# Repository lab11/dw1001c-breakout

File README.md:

DWM1001 Breakout
================

Hardware files can be found in `hardware`.

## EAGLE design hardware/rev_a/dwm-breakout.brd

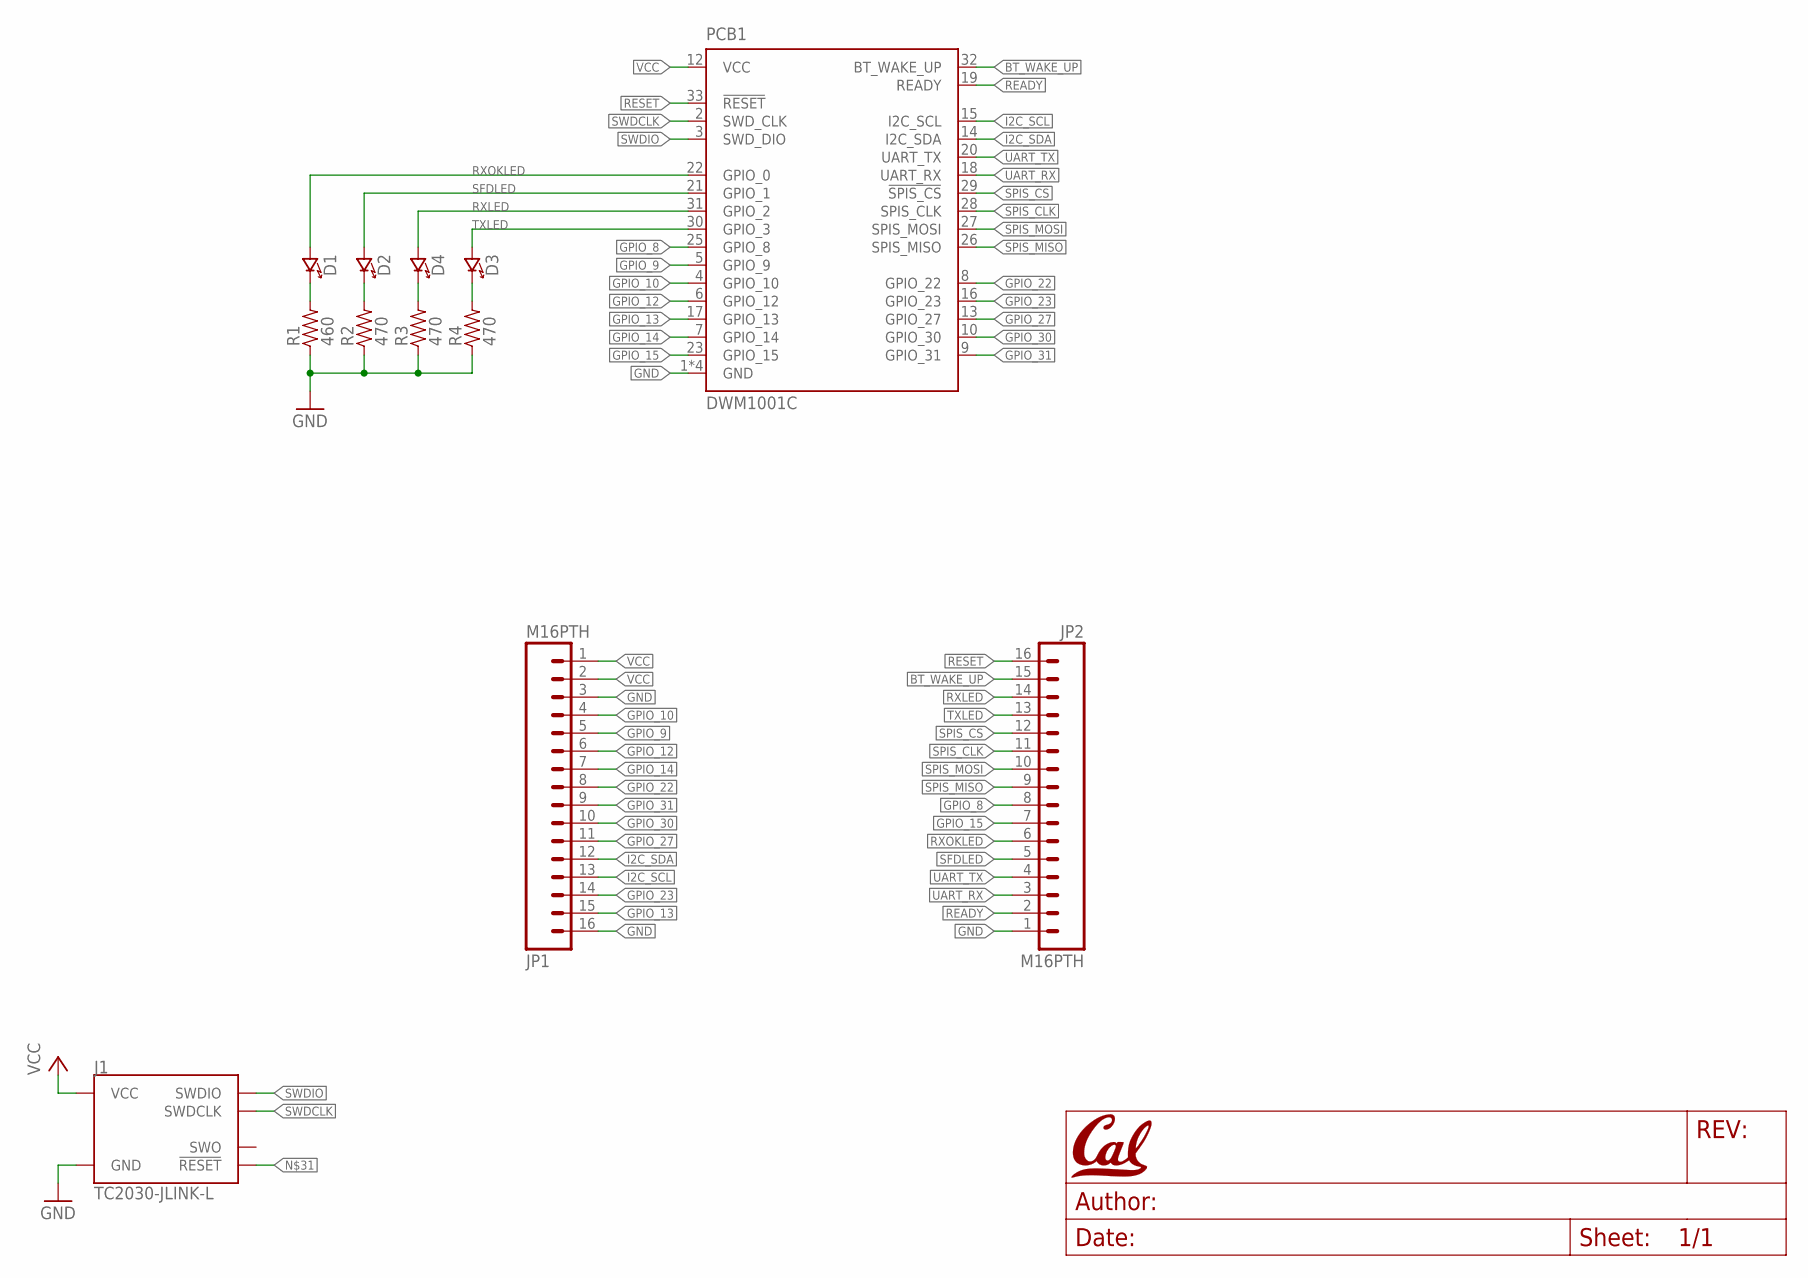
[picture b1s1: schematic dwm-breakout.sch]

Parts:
D1: LED0603; LED-0603; MPN LTST-C104KRKT; DIGIKEY 160-1835-6-ND
D2: LED0603; LED-0603; MPN LTST-C194TBKT; DIGIKEY 160-1837-6-ND
D3: LED0603; LED-0603; MPN LTST-C190YKT; DIGIKEY 160-1184-6-ND
D4: LED0603; LED-0603; MPN LTST-C194KGKT; DIGIKEY 160-1834-6-ND
J1: TC2030-JLINK-L; TC2030-IDC
JP1, JP2: M16PTH; 1X16
PCB1: DWM1001C
R1: 460; 0402_RES; MPN MCR01MZPJ471; DIGIKEY RHM470JCT-ND
R2, R3, R4: 470; 0402_RES; MPN MCR01MZPJ471; DIGIKEY RHM470JCT-ND

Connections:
!RESET: JP2.16, PCB1.33 (!RESET)
!SPIS_CS: JP2.12, PCB1.29 (!SPIS_CS)
BT_WAKE_UP: JP2.15, PCB1.32 (BT_WAKE_UP)
GND: J1.5 (GND), JP1.3, JP1.16, JP2.1, PCB1.1 (GND), PCB1.11 (GND), PCB1.24 (GND), PCB1.34 (GND), R1.1, R2.1, R3.1, R4.1
GPIO_8: JP2.8, PCB1.25 (GPIO_8)
GPIO_9: JP1.5, PCB1.5 (GPIO_9)
GPIO_10: JP1.4, PCB1.4 (GPIO_10)
GPIO_12: JP1.6, PCB1.6 (GPIO_12)
GPIO_13: JP1.15, PCB1.17 (GPIO_13)
GPIO_14: JP1.7, PCB1.7 (GPIO_14)
GPIO_15: JP2.7, PCB1.23 (GPIO_15)
GPIO_22: JP1.8, PCB1.8 (GPIO_22)
GPIO_23: JP1.14, PCB1.16 (GPIO_23)
GPIO_27: JP1.11, PCB1.13 (GPIO_27)
GPIO_30: JP1.10, PCB1.10 (GPIO_30)
GPIO_31: JP1.9, PCB1.9 (GPIO_31)
I2C_SCL: JP1.13, PCB1.15 (I2C_SCL)
I2C_SDA: JP1.12, PCB1.14 (I2C_SDA)
unnamed: D1.C (CATHODE), R1.2
unnamed: D2.C (CATHODE), R2.2
unnamed: D4.C (CATHODE), R3.2
unnamed: D3.C (CATHODE), R4.2
READY: JP2.2, PCB1.19 (READY)
RXLED: D4.A (ANODE), JP2.14, PCB1.31 (GPIO_2)
RXOKLED: D1.A (ANODE), JP2.6, PCB1.22 (GPIO_0)
SFDLED: D2.A (ANODE), JP2.5, PCB1.21 (GPIO_1)
SPIS_CLK: JP2.11, PCB1.28 (SPIS_CLK)
SPIS_MISO: JP2.9, PCB1.26 (SPIS_MISO)
SPIS_MOSI: JP2.10, PCB1.27 (SPIS_MOSI)
SWDCLK: J1.4 (SWDCLK), PCB1.2 (SWD_CLK)
SWDIO: J1.2 (SWDIO), PCB1.3 (SWD_DIO)
TXLED: D3.A (ANODE), JP2.13, PCB1.30 (GPIO_3)
UART_RX: JP2.3, PCB1.18 (UART_RX)
UART_TX: JP2.4, PCB1.20 (UART_TX)
VCC: J1.1 (VCC), JP1.1, JP1.2, PCB1.12 (VCC)

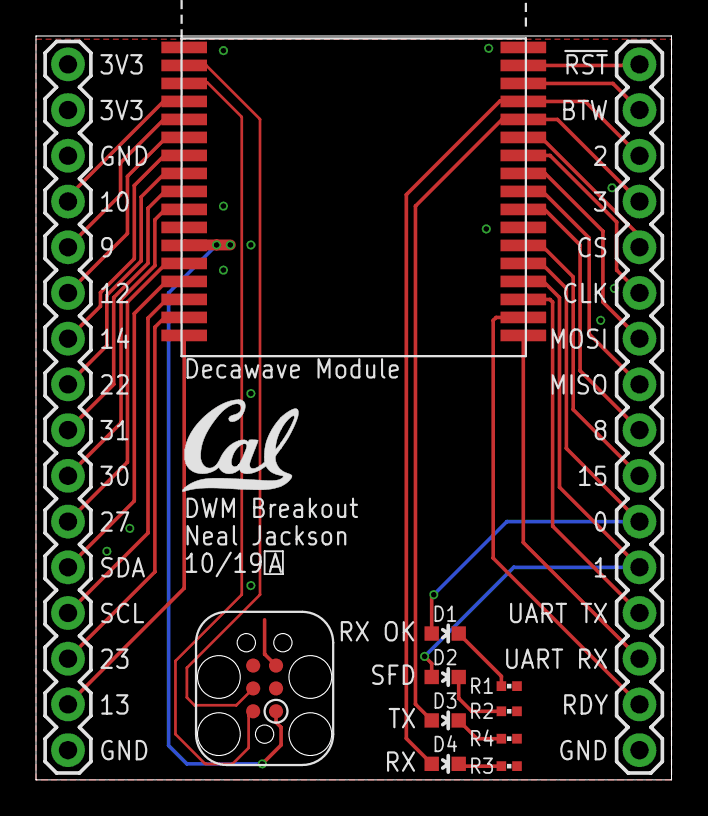
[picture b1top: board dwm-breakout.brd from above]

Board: 2 copper layers, 35.3 x 41.3 mm, 13 parts (0 on the bottom side), 35 nets.

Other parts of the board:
U$2: UCB_CAL_200MIL

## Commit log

2019-10-31 add empty-ish readme
2019-11-01 Designed, routed, and bundled
2019-11-01 Move LED+resistors

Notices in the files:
parts and their libraries:
SparkFun-Connectors: Licensing: CC v3.0 Share-Alike You are welcome to use this library for commercial purposes.
